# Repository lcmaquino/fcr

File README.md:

## Description

The Fenix Reballing Controller (FCR) software controls the temperature of two heating devices for preheating electronic boards or reballing BGA components. Examples of heating devices include an electric grill or an electric resistor. Due to the high electrical current required to power these devices, they should be activated via a mechanical relay or a solid-state relay.

The FCR consists of an electronic circuit with the [Raspberry Pi Pico](https://projects.raspberrypi.org/en/projects/getting-started-with-the-pico) microcontroller and a set of codes written for [MicroPython](https://www.micropython.org/).

## Assembly and Installation

  - Assemble the electronic circuit according to the schematic diagram: [fenix-controlador-de-ressolda.pdf](https://github.com/lcmaquino/fcr/tree/main/pcb/fenix-controlador-de-ressolda.pdf). Also, see the [simple wiring diagram](assets/fcr-simple-wiring.png);
  - Connect the relay input pins to the connectors indicated in the diagram by `OUT1` and `OUT2`;
  - Connect the relay output pins to the heating devices;
  - Connect the HD44780 LCD 16×02, MAX6675, and Keyes_AD_Key modules to their respective connectors indicated in the diagram;
  - Install the [MicroPython firmware](https://projects.raspberrypi.org/en/projects/getting-started-with-the-pico/3) on the Raspberry Pi Pico;
  - Use your preferred IDE to copy all files from the [`src`](https://github.com/lcmaquino/fcr/tree/main/src) directory to the Raspberry Pi Pico. (For example, you can use [Thonny](https://thonny.org/) or [Visual Studio Code](https://code.visualstudio.com/));
  - Power the electronic circuit with a 5V DC power supply with at least 500mA;

  The Keyes_AD_Key module has five tactile switches labeled SW1, SW2, SW3, SW4, and SW5. The FCR maps these switches for menu navigation such that:

  - SW1 - moves the menu to the left;
  - SW2 - increases the value of the currently displayed option;
  - SW3 - decreases the value of the currently displayed option;
  - SW4 - moves the menu to the right;
  - SW5 - selects the current menu;

## Usage

  The FCR has three modes:
  - Preheater - for preheating an electronic board;
  - Reballing - for reballing BGA components;
  - Auto Tuning - to automatically calculate the coefficients used in the [PID](https://en.wikipedia.org/wiki/Proportional-integral-derivative_controller) control;

  All modes have a menu containing specific and general options.

  The general options are:
  - `Kp` - proportional coefficient of the PID control;
  - `Ki` - integral coefficient of the PID control;
  - `Kd` - derivative coefficient of the PID control;
  - `ap` - actuation period is the period (in seconds) at which the PID control is updated;
  - `Run` - execute the mode functions;
  - `Home` - return to the initial mode selection screen;

  See below the specific options for each mode.

### Preheater Mode

  The Preheater mode controls only one heating device that should be placed below the electronic board.

  In Preheater mode, the specific options are:
  - `SV` - Setpoint Variable is the temperature (in degrees Celsius) that the heating element should reach;
  - `d` - duration is the duration (in seconds) the mode should run;

### Reballing Mode

  The Reballing mode controls two heating devices, one of which should be placed below the electronic board and the other above it.

  In Reballing mode, the specific options are:
  - `PTN` - pattern is the temperature pattern (in degrees Celsius) that the heating devices should follow. Each pattern consists of up to five parts, each containing the `r`, `L`, and `d` options explained below;
  - `r` - rate is the rate of temperature change (in degrees Celsius per second);
  - `L` - limit is the temperature limit (in degrees Celsius) that should be reached;
  - `d` - duration is the duration (in seconds) that the temperature should remain at its limit `L`;

  Up to 10 temperature patterns can be configured. Here is an example configuration:
```
  PTN1
  | - r1: 0.86
  | - L1: 120.0
  | - d1: 60
  | - r2: 0.57
  | - L2: 180.0
  | - d2: 60
  | - r3: 0.29
  | - L3: 210.0
  | - d3: 60
  | - r4: 0.19
  | - L4: 227.0
  | - d4: 60
  | - r5: 0.0
  | - L5: 0.0
  | - d5: 0
```

  Note that in this example, the PTN1 pattern will have four active parts. The fifth part is all zeros and will be ignored by the FCR. The figure below represents this pattern.

  In the first part of the pattern, the temperature should rise at a rate of `r1 = 0.86`°C/s until it reaches `L1 = 120`°C, staying at this temperature for `d1 = 60`s. In the second part, the temperature should rise at a rate of `r2 = 0.57`°C/s until it reaches `L2 = 180`°C, staying at this temperature for `d2 = 60`s. In the third part, the temperature should rise at a rate of `r3 = 0.29`°C/s until it reaches `L3 = 210`°C, staying at this temperature for `d3 = 60`s. Finally, in the fourth part, the temperature should rise at a rate of `r4 = 0.19`°C/s until it reaches `L4 = 227`°C, staying at this temperature for `d4 = 60`s.

### Auto Tuning

  The Auto Tuning mode analyzes the temperature data of the heating device below the electronic board to approximately calculate the `Kp`, `Ki`, and `Kd` coefficients of the PID controller.

  In Auto Tuning mode, the specific options are:
  - `SV` - Setpoint Variable is the temperature (in degrees Celsius) that the heating element should reach;
  - `d` - duration is the duration (in seconds) the mode should run;

## License

FCR is open-sourced software licensed under the [GPL v3.0 or later](https://github.com/lcmaquino/ccolab/blob/main/LICENSE).

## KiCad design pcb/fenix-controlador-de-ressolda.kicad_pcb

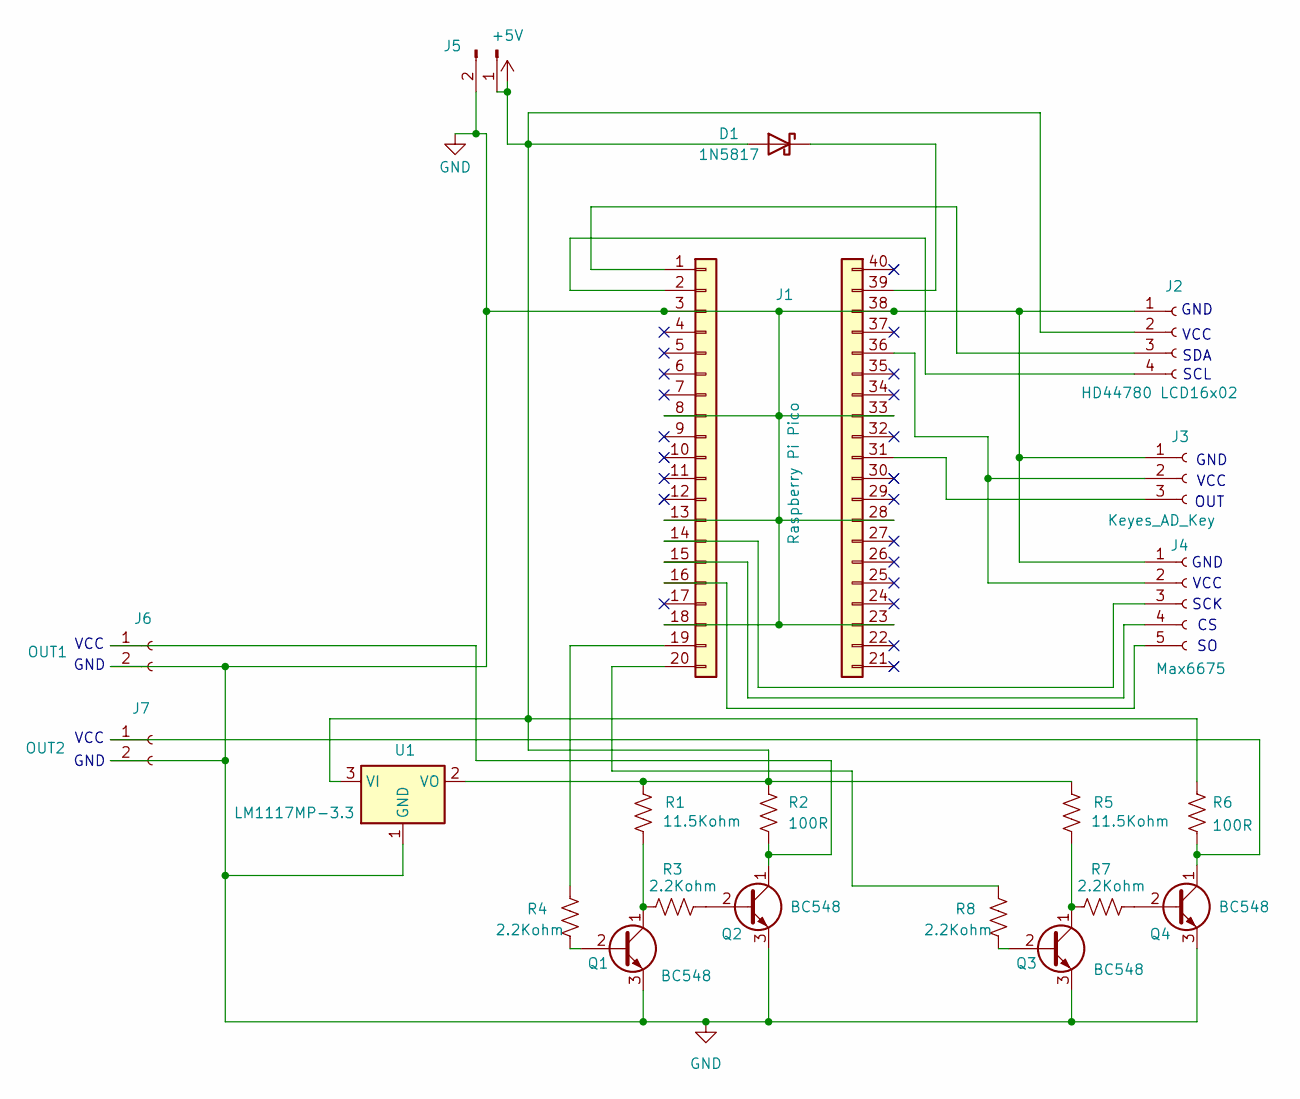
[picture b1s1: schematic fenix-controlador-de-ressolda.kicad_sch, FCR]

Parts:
D1: 1N5817; D_DO-41_SOD81_P10.16mm_Horizontal
J1: Raspberry Pi Pico; PinSocket_1x20_P2.54mm_Vertical
J2: HD44780 LCD16x02; PinSocket_1x04_P2.54mm_Vertical
J3: Keyes_AD_Key; PinSocket_1x03_P2.54mm_Vertical
J4: Max6675; PinSocket_1x05_P2.54mm_Vertical
J5: Conn_01x02_Pin; PinHeader_1x02_P2.54mm_Vertical
J6: OUT1; PinSocket_1x02_P2.54mm_Vertical
J7: OUT2; PinSocket_1x02_P2.54mm_Vertical
J9: Conn_01x20; PinSocket_1x20_P2.54mm_Vertical
Q1, Q2, Q3, Q4: BC548; TO-92_Inline
R1, R5: 11.5Kohm; R_Axial_DIN0207_L6.3mm_D2.5mm_P7.62mm_Horizontal
R2, R6: 100R; R_Axial_DIN0207_L6.3mm_D2.5mm_P7.62mm_Horizontal
R3, R4, R7, R8: 2.2Kohm; R_Axial_DIN0207_L6.3mm_D2.5mm_P7.62mm_Horizontal
U1: LM1117MP-3.3; SOT-223-3_TabPin2

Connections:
GND: J1.3, J1.8, J1.13, J1.18, J2.1, J3.1, J4.1, J5.2, J6.2, J7.2, J9.23, J9.28, J9.33, J9.38, Q1.3 (E), Q2.3 (E), Q3.3 (E), Q4.3 (E), U1.1 (GND)
unnamed: D1.1 (K), J9.39
unnamed: J1.1, J2.3
unnamed: J1.2, J2.4
unnamed: J1.14, J4.3
unnamed: J1.15, J4.4
unnamed: J1.16, J4.5
unnamed: J1.19, R4.1
unnamed: J1.20, R8.1
unnamed: J3.2, J4.2, J9.36
unnamed: J3.3, J9.31
unnamed: J6.1, Q2.1 (C), R2.2
unnamed: J7.1, Q4.1 (C), R6.2
unnamed: Q1.2 (B), R4.2
unnamed: Q1.1 (C), R1.2, R3.1
unnamed: Q2.2 (B), R3.2
unnamed: Q3.2 (B), R8.2
unnamed: Q3.1 (C), R5.2, R7.1
unnamed: Q4.2 (B), R7.2

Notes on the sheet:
VCC
GND
SDA
SCK
SCL
OUT

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
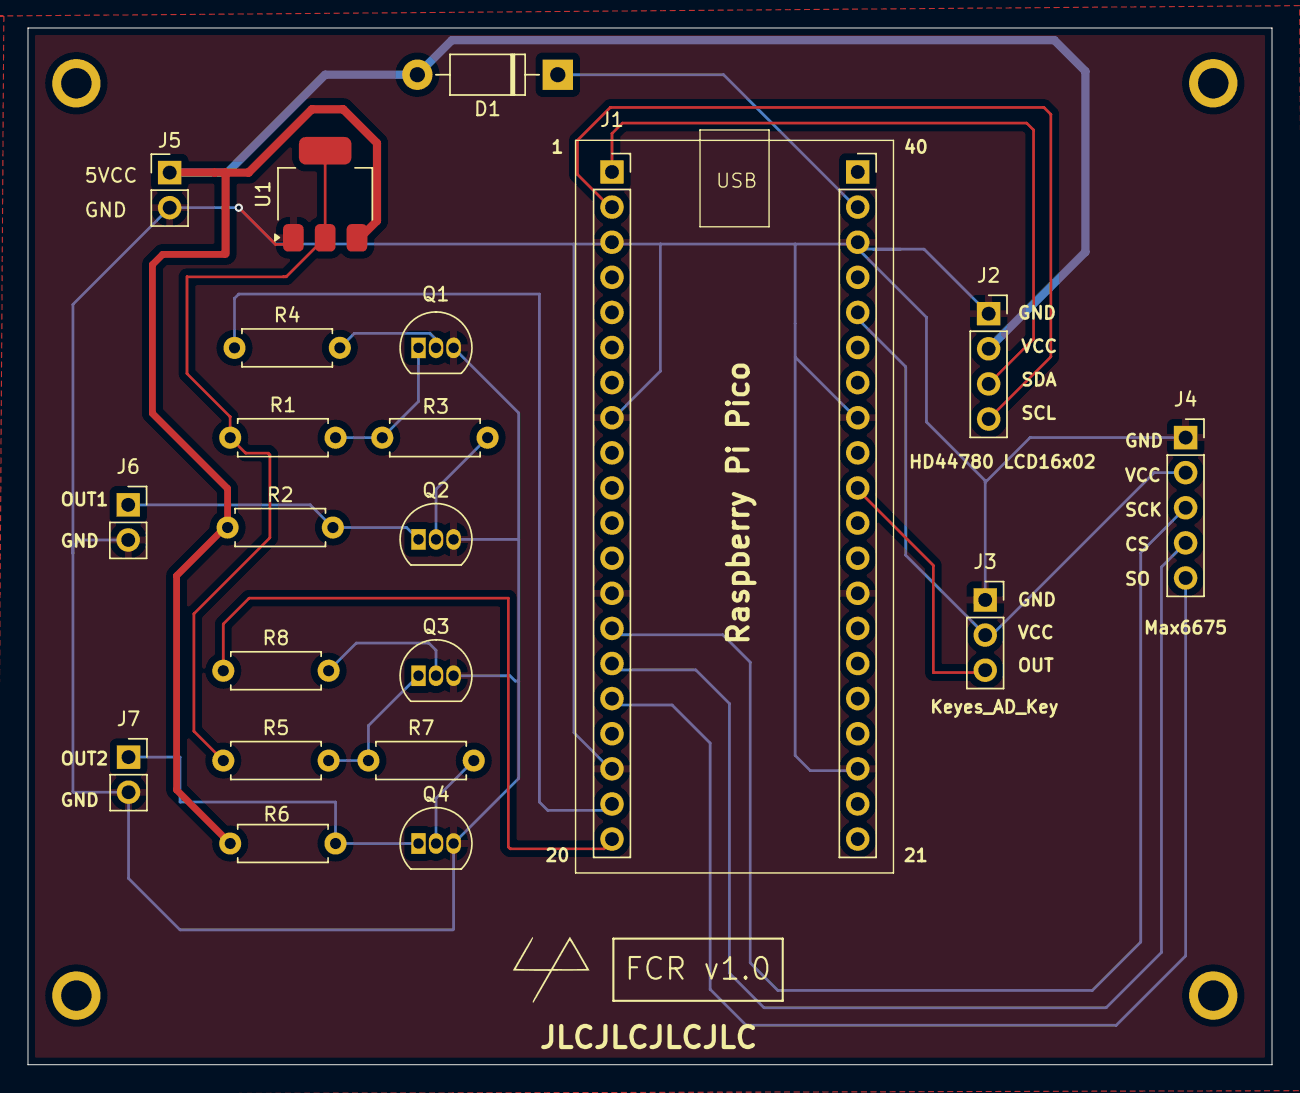
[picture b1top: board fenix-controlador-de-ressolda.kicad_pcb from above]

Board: 4 copper layers, 90.0 x 75.0 mm, 22 parts (0 on the bottom side), 21 nets.

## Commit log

2025-01-06 Let the fun begin!
2025-01-06 Minor README.md change.
2025-01-06 Minor README_PTBR.md change
2025-01-07 Add a simple wiring diagram.
